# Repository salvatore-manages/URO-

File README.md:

# URO 🪐

A little AI companion for the real world.

«What if AI wasn't just inside our phones, but somthing we can actually carry with us?»

# 💡 About URO

URO is an AI wearable I'm trying to build. The idea is to make a small device that you can talk to, ask questions, take pictures with, and get AI-powered responces without having to do everything on your phone.

It's supposed to connect with an Android app, which handles the AI, internet and other processings, while the device itself handles voice input, audio output, camera and comunication.

I'm still figuring out alot of things, but that's what makes this project intresting to me.

# ✨ Features I'm Working On

- 🎙️ Voice interaction in English, Hindi and Hinglish.
- 🧠 AI-powered conversations and research using Gemini.
- 📸 Camera for taking pictures and asking questions about them.
- 🔊 Audio responces through a small speaker.
- 📱 Android application for connecting everything together.
- 🔵 Bluetooth comunication between the device and phone.
- 🎭 An animated AI character with its own personality.

# ⚙️ How It Works

Voice / Photo
      ↓
   URO Device
      ↓ Bluetooth
 Android App
      ↓
  Gemini AI
      ↓
Response → App → URO

# 🛠️ Tech & Hardware

Component| Technology
Microcontroller| ESP32-S3 (planned)
AI| Gemini
Connectivity| Bluetooth LE
Application| Android
Firmware| Embedded C/C++
PCB| Custom PCB design
Enclosure| 3D CAD design

# 🚧 Current Status

URO is currently in its design and developement phase. I'm working on the PCB, schematics, CAD, firmware and the software architechture.

The physical prototype isn't build yet. There is still alot to figure out, test and probably redesign.

🌱 Why I'm Building It

I'm a student trying to build something way beyond what I already know, and honestly, I'm learning as I go.

This project is my attempt to bring together AI, electronics, software and design into something real. I don't know exactly how difficult every part will be, but I want to try, make mistakes, fix them and see where this idea goes.

This is URO. Still building, still learning.

---

Built with curiosity, countless ideas and a lot of debugging.
(hehehe I'm kinda intelligent bruhh)
# Cooked by Raghav

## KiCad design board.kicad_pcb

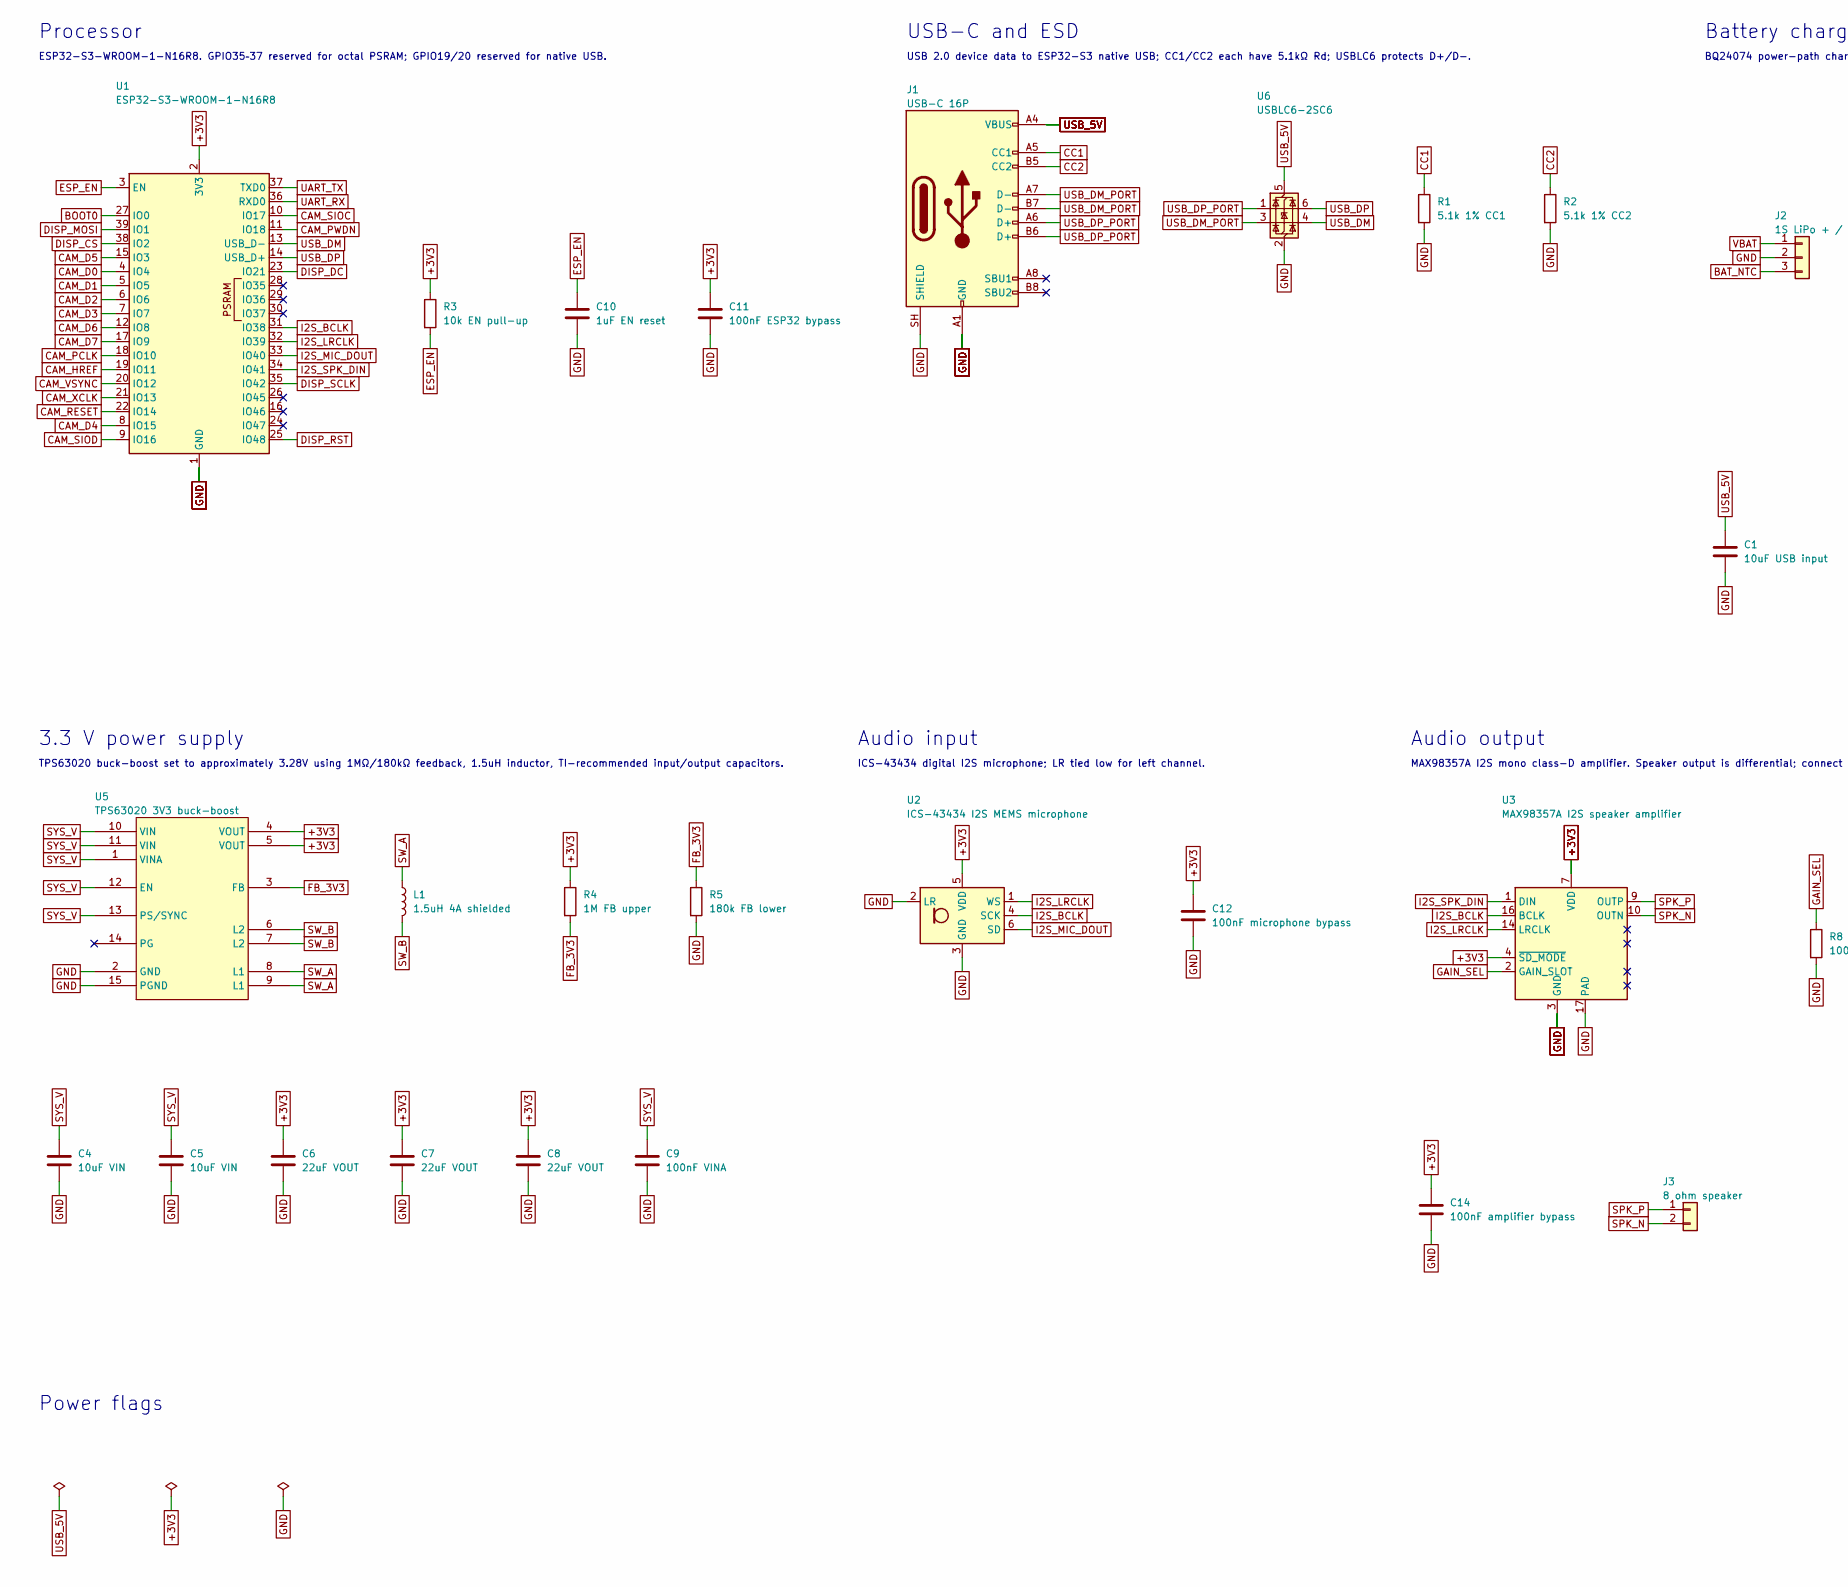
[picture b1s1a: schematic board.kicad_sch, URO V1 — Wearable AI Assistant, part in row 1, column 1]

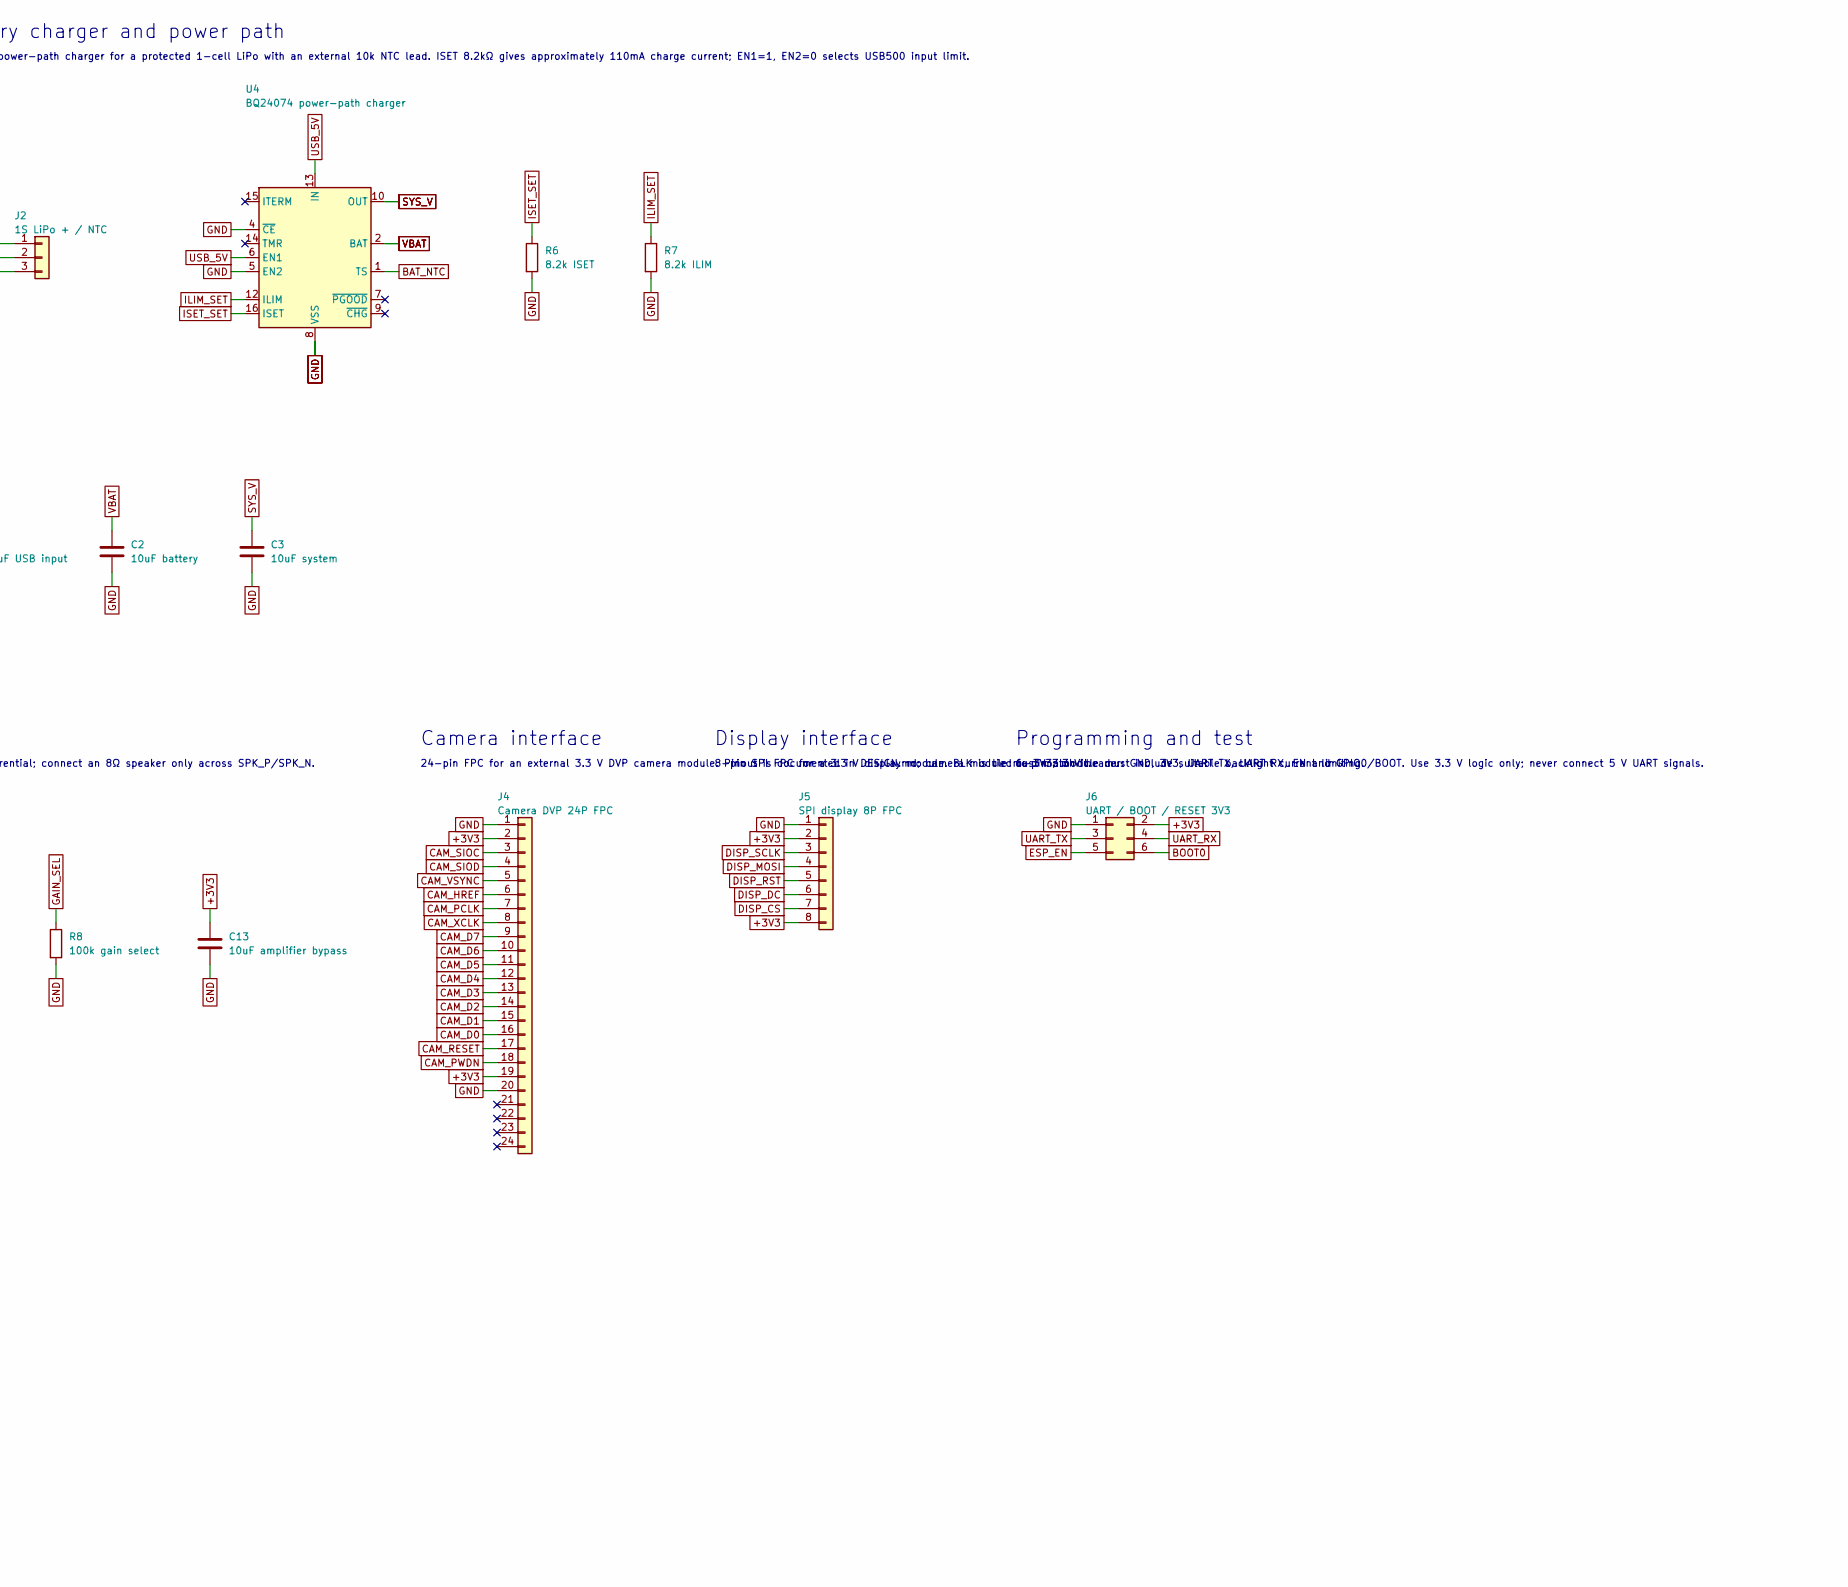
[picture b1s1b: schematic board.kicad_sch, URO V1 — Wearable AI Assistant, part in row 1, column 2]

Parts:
C1: 10uF USB input; C_0805_2012Metric
C2: 10uF battery; C_0805_2012Metric
C3: 10uF system; C_0805_2012Metric
C4, C5: 10uF VIN; C_0805_2012Metric
C6, C7, C8: 22uF VOUT; C_0805_2012Metric
C9: 100nF VINA; C_0603_1608Metric
C10: 1uF EN reset; C_0603_1608Metric
C11: 100nF ESP32 bypass; C_0603_1608Metric
C12: 100nF microphone bypass; C_0603_1608Metric
C13: 10uF amplifier bypass; C_0805_2012Metric
C14: 100nF amplifier bypass; C_0603_1608Metric
J1: USB-C 16P; USB_C_Receptacle_HRO_TYPE-C-31-M-12; MPN TYPE-C-31-M-12
J2: 1S LiPo + / NTC; JST_PH_B3B-PH-K_1x03_P2.00mm_Vertical; MPN JST PH 3-pin battery connector
J3: 8 ohm speaker; JST_PH_S2B-PH-K_1x02_P2.00mm_Horizontal
J4: Camera DVP 24P FPC; Hirose_FH12-24S-0.5SH_1x24-1MP_P0.50mm_Horizontal
J5: SPI display 8P FPC; Hirose_FH12-8S-0.5SH_1x08-1MP_P0.50mm_Horizontal
J6: UART / BOOT / RESET 3V3; PinHeader_2x03_P2.54mm_Vertical
L1: 1.5uH 4A shielded; L_1210_3225Metric; MPN FPB322520D-1R5MT0; LCSC C29780742
R1: 5.1k 1% CC1; R_0603_1608Metric; MPN 0603 5.1k 1%; LCSC C23186
R2: 5.1k 1% CC2; R_0603_1608Metric; MPN 0603 5.1k 1%; LCSC C23186
R3: 10k EN pull-up; R_0603_1608Metric
R4: 1M FB upper; R_0603_1608Metric
R5: 180k FB lower; R_0603_1608Metric
R6: 8.2k ISET; R_0603_1608Metric
R7: 8.2k ILIM; R_0603_1608Metric
R8: 100k gain select; R_0603_1608Metric
U1: ESP32-S3-WROOM-1-N16R8; ESP32-S3-WROOM-1; MPN ESP32-S3-WROOM-1-N16R8; LCSC C2913202
U2: ICS-43434 I2S MEMS microphone; MIC-SMD_6P-L3.5-W2.7-P0.90-BL; MPN ICS-43434; LCSC C5656610
U3: MAX98357A I2S speaker amplifier; TQFN-16-1EP_3x3mm_P0.5mm_EP1.23x1.23mm; MPN MAX98357AETE+T; LCSC C910544
U4: BQ24074 power-path charger; VQFN-16-1EP_3x3mm_P0.5mm_EP1.6x1.6mm; MPN BQ24074RGTT; LCSC C2861252
U5: TPS63020 3V3 buck-boost; VSON-14_L4.0-W3.0-P0.50-BL-EP_TI_DSJ; MPN TPS63020DSJR; LCSC C15483
U6: USBLC6-2SC6; SOT-23-6; MPN USBLC6-2SC6; LCSC C2687116

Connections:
+3V3: C6.1, C7.1, C8.1, C11.1, C12.1, C13.1, C14.1, J4.2, J4.19, J5.2, J5.8, J6.2, R3.1, R4.1, U1.2 (3V3), U2.5 (VDD), U3.4 (~SD_MODE), U3.7 (VDD), U3.8 (VDD), U5.4 (VOUT), U5.5 (VOUT)
BAT_NTC: J2.3, U4.1 (TS)
BOOT0: J6.6, U1.27 (IO0)
CAM_D0: J4.16, U1.4 (IO4)
CAM_D1: J4.15, U1.5 (IO5)
CAM_D2: J4.14, U1.6 (IO6)
CAM_D3: J4.13, U1.7 (IO7)
CAM_D4: J4.12, U1.8 (IO15)
CAM_D5: J4.11, U1.15 (IO3)
CAM_D6: J4.10, U1.12 (IO8)
CAM_D7: J4.9, U1.17 (IO9)
CAM_HREF: J4.6, U1.19 (IO11)
CAM_PCLK: J4.7, U1.18 (IO10)
CAM_PWDN: J4.18, U1.11 (IO18)
CAM_RESET: J4.17, U1.22 (IO14)
CAM_SIOC: J4.3, U1.10 (IO17)
CAM_SIOD: J4.4, U1.9 (IO16)
CAM_VSYNC: J4.5, U1.20 (IO12)
CAM_XCLK: J4.8, U1.21 (IO13)
CC1: J1.A5 (CC1), R1.1
CC2: J1.B5 (CC2), R2.1
DISP_CS: J5.7, U1.38 (IO2)
DISP_DC: J5.6, U1.23 (IO21)
DISP_MOSI: J5.4, U1.39 (IO1)
DISP_RST: J5.5, U1.25 (IO48)
DISP_SCLK: J5.3, U1.35 (IO42)
ESP_EN: C10.1, J6.5, R3.2, U1.3 (EN)
FB_3V3: R4.2, R5.1, U5.3 (FB)
GAIN_SEL: R8.1, U3.2 (GAIN_SLOT)
GND: C1.2, C2.2, C3.2, C4.2, C5.2, C6.2, C7.2, C8.2, C9.2, C10.2, C11.2, C12.2, C13.2, C14.2, J1.A1 (GND), J1.A12 (GND), J1.B1 (GND), J1.B12 (GND), J1.SH (SHIELD), J2.2, J4.1, J4.20, J5.1, J6.1, R1.2, R2.2, R5.2, R6.2, R7.2, R8.2, U1.1 (GND), U1.40 (GND), U1.41 (GND), U2.2 (LR), U2.3 (GND), U3.3 (GND), U3.11 (GND), U3.15 (GND), U3.17 (PAD), U4.4 (~CE), U4.5 (EN2), U4.8 (VSS), U4.17 (VSS), U5.2 (GND), U5.15 (PGND), U6.2 (GND)
I2S_BCLK: U1.31 (IO38), U2.4 (SCK), U3.16 (BCLK)
I2S_LRCLK: U1.32 (IO39), U2.1 (WS), U3.14 (LRCLK)
I2S_MIC_DOUT: U1.33 (IO40), U2.6 (SD)
I2S_SPK_DIN: U1.34 (IO41), U3.1 (DIN)
ILIM_SET: R7.1, U4.12 (ILIM)
ISET_SET: R6.1, U4.16 (ISET)
SPK_N: J3.2, U3.10 (OUTN)
SPK_P: J3.1, U3.9 (OUTP)
SW_A: L1.1, U5.8 (L1), U5.9 (L1)
SW_B: L1.2, U5.6 (L2), U5.7 (L2)
SYS_V: C3.1, C4.1, C5.1, C9.1, U4.10 (OUT), U4.11 (OUT), U5.1 (VINA), U5.10 (VIN), U5.11 (VIN), U5.12 (EN), U5.13 (PS/SYNC)
UART_RX: J6.4, U1.36 (RXD0)
UART_TX: J6.3, U1.37 (TXD0)
USB_5V: C1.1, J1.A4 (VBUS), J1.A9 (VBUS), J1.B4 (VBUS), J1.B9 (VBUS), U4.6 (EN1), U4.13 (IN), U6.5 (VBUS)
USB_DM: U1.13 (USB_D-), U6.4 (I/O2)
USB_DM_PORT: J1.A7 (D-), J1.B7 (D-), U6.3 (I/O2)
USB_DP: U1.14 (USB_D+), U6.6 (I/O1)
USB_DP_PORT: J1.A6 (D+), J1.B6 (D+), U6.1 (I/O1)
VBAT: C2.1, J2.1, U4.2 (BAT), U4.3 (BAT)

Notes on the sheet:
Processor
ESP32-S3-WROOM-1-N16R8. GPIO35–37 reserved for octal PSRAM; GPIO19/20 reserved for native USB.
USB-C and ESD
USB 2.0 device data to ESP32-S3 native USB; CC1/CC2 each have 5.1kΩ Rd; USBLC6 protects D+/D−.
Battery charger and power path
BQ24074 power-path charger for a protected 1-cell LiPo with an external 10k NTC lead. ISET 8.2kΩ gives approximately 110mA charge current; EN1=1, EN2=0 selects USB500 input limit.
3.3 V power supply
TPS63020 buck-boost set to approximately 3.28V using 1MΩ/180kΩ feedback, 1.5uH inductor, TI-recommended input/output capacitors.
Audio input
ICS-43434 digital I2S microphone; LR tied low for left channel.
Audio output
MAX98357A I2S mono class-D amplifier. Speaker output is differential; connect an 8Ω speaker only across SPK_P/SPK_N.
Camera interface
24-pin FPC for an external 3.3 V DVP camera module. Pinout is documented in DESIGN.md; camera module must match it.
Display interface
8-pin SPI FPC for a 3.3 V display module. BLK is tied to 3V3; module must include suitable backlight current limiting.
Programming and test
6-pin 3.3 V header: GND, 3V3, UART TX, UART RX, EN and GPIO0/BOOT. Use 3.3 V logic only; never connect 5 V UART signals.
Power flags

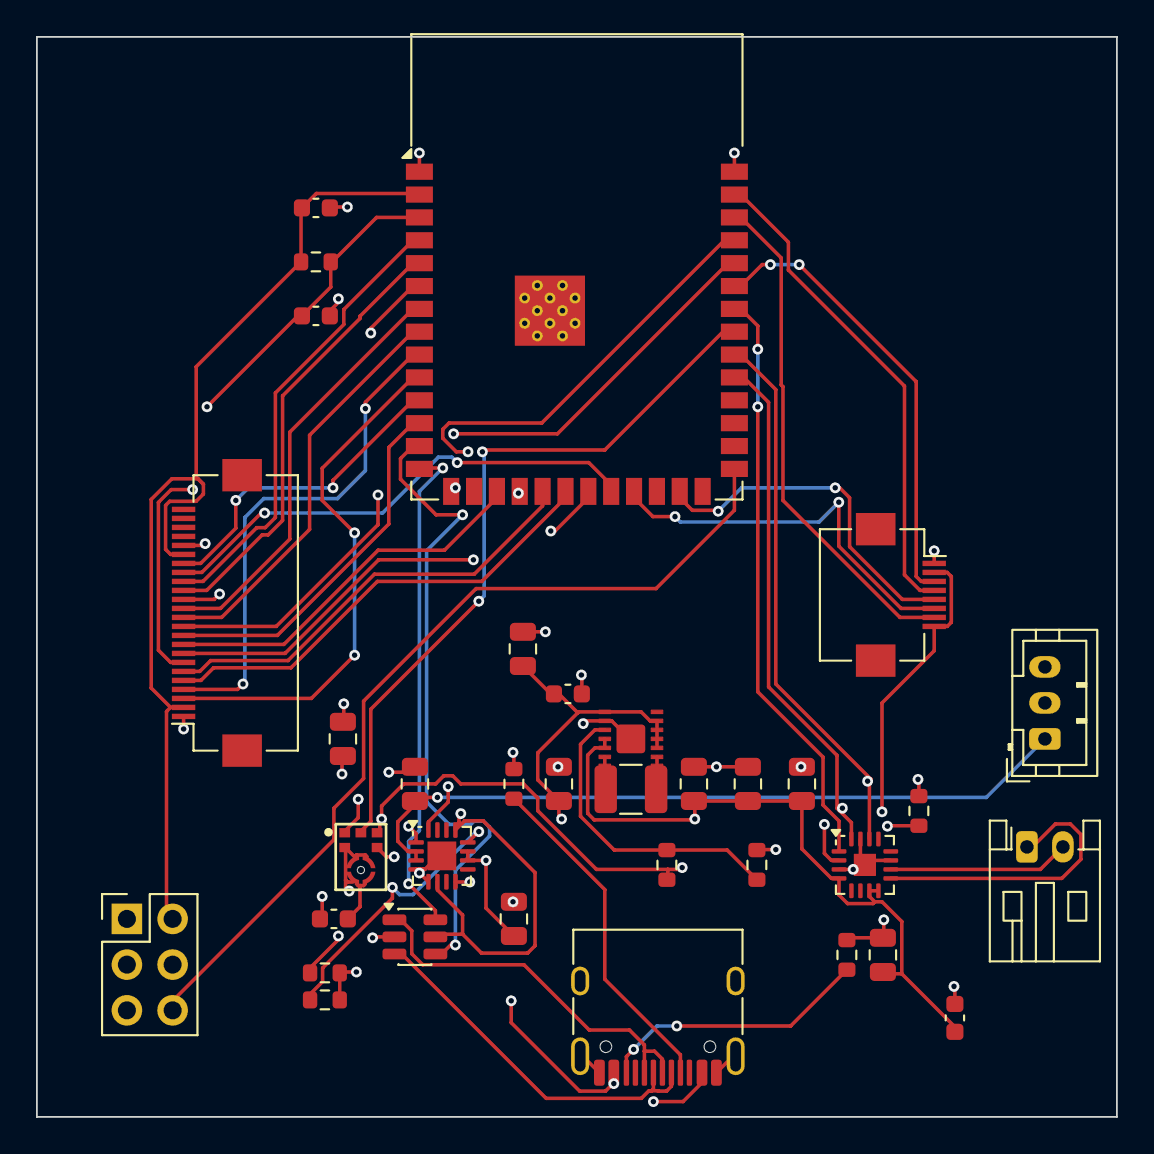
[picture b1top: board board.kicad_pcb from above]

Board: 4 copper layers, 60.0 x 60.0 mm, 35 parts (0 on the bottom side), 49 nets.

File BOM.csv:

Designators,Value,Manufacturer Part Number,Footprint,Qty,LCSC Part Number,Notes
C1,10uF USB input,,Capacitor_SMD:C_0805_2012Metric,1,,Manufacturer part number and electrical rating are not specified; select and verify before ordering.
C10,1uF EN reset,,Capacitor_SMD:C_0603_1608Metric,1,,Manufacturer part number and electrical rating are not specified; select and verify before ordering.
C11,100nF ESP32 bypass,,Capacitor_SMD:C_0603_1608Metric,1,,Manufacturer part number and electrical rating are not specified; select and verify before ordering.
C12,100nF microphone bypass,,Capacitor_SMD:C_0603_1608Metric,1,,Manufacturer part number and electrical rating are not specified; select and verify before ordering.
C13,10uF amplifier bypass,,Capacitor_SMD:C_0805_2012Metric,1,,Manufacturer part number and electrical rating are not specified; select and verify before ordering.
C14,100nF amplifier bypass,,Capacitor_SMD:C_0603_1608Metric,1,,Manufacturer part number and electrical rating are not specified; select and verify before ordering.
C2,10uF battery,,Capacitor_SMD:C_0805_2012Metric,1,,Manufacturer part number and electrical rating are not specified; select and verify before ordering.
C3,10uF system,,Capacitor_SMD:C_0805_2012Metric,1,,Manufacturer part number and electrical rating are not specified; select and verify before ordering.
"C4, C5",10uF VIN,,Capacitor_SMD:C_0805_2012Metric,2,,Manufacturer part number and electrical rating are not specified; select and verify before ordering.
"C6, C7, C8",22uF VOUT,,Capacitor_SMD:C_0805_2012Metric,3,,Manufacturer part number and electrical rating are not specified; select and verify before ordering.
C9,100nF VINA,,Capacitor_SMD:C_0603_1608Metric,1,,Manufacturer part number and electrical rating are not specified; select and verify before ordering.
J1,USB-C 16P,TYPE-C-31-M-12,Connector_USB:USB_C_Receptacle_HRO_TYPE-C-31-M-12,1,,
J2,1S LiPo + / NTC,JST PH 3-pin battery connector,parts:JST_PH_B3B-PH-K_1x03_P2.00mm_Vertical,1,,Requires a protected 1-cell LiPo pack with compatible 10k NTC lead; verify connector polarity and pack dimensions.
J3,8 ohm speaker,,parts:JST_PH_S2B-PH-K_1x02_P2.00mm_Horizontal,1,,Speaker connector only; verify speaker impedance and rated power before fitting.
J4,Camera DVP 24P FPC,,Connector_FFC-FPC:Hirose_FH12-24S-0.5SH_1x24-1MP_P0.50mm_Horizontal,1,,Connector only. Camera sensor/module and flex contact orientation are not yet selected.
J5,SPI display 8P FPC,,Connector_FFC-FPC:Hirose_FH12-8S-0.5SH_1x08-1MP_P0.50mm_Horizontal,1,,"Connector only. Display controller, resolution, flex orientation and backlight current must be confirmed."
J6,UART / BOOT / RESET 3V3,,Connector_PinHeader_2.54mm:PinHeader_2x03_P2.54mm_Vertical,1,,"2x3 programming header: GND, 3V3, UART_TX, UART_RX, ESP_EN, BOOT0. 3.3V logic only."
L1,1.5uH 4A shielded,FPB322520D-1R5MT0,Inductor_SMD:L_1210_3225Metric,1,C29780742,
R1,5.1k 1% CC1,0603 5.1k 1%,Resistor_SMD:R_0603_1608Metric,1,C23186,
R2,5.1k 1% CC2,0603 5.1k 1%,Resistor_SMD:R_0603_1608Metric,1,C23186,
R3,10k EN pull-up,,Resistor_SMD:R_0603_1608Metric,1,,Manufacturer part number and electrical rating are not specified; select and verify before ordering.
R4,1M FB upper,,Resistor_SMD:R_0603_1608Metric,1,,Manufacturer part number and electrical rating are not specified; select and verify before ordering.
R5,180k FB lower,,Resistor_SMD:R_0603_1608Metric,1,,Manufacturer part number and electrical rating are not specified; select and verify before ordering.
R6,8.2k ISET,,Resistor_SMD:R_0603_1608Metric,1,,Manufacturer part number and electrical rating are not specified; select and verify before ordering.
R7,8.2k ILIM,,Resistor_SMD:R_0603_1608Metric,1,,Manufacturer part number and electrical rating are not specified; select and verify before ordering.
R8,100k gain select,,Resistor_SMD:R_0603_1608Metric,1,,Manufacturer part number and electrical rating are not specified; select and verify before ordering.
U1,ESP32-S3-WROOM-1-N16R8,ESP32-S3-WROOM-1-N16R8,RF_Module:ESP32-S3-WROOM-1,1,C2913202,ESP32-S3-WROOM-1-N16R8 module; verify exact module marking and antenna keep-out.
U2,ICS-43434 I2S MEMS microphone,ICS-43434,parts:MIC-SMD_6P-L3.5-W2.7-P0.90-BL,1,C5656610,
U3,MAX98357A I2S speaker amplifier,MAX98357AETE+T,parts:TQFN-16-1EP_3x3mm_P0.5mm_EP1.23x1.23mm,1,C910544,
U4,BQ24074 power-path charger,BQ24074RGTT,parts:VQFN-16-1EP_3x3mm_P0.5mm_EP1.6x1.6mm,1,C2861252,BQ24074 charger/power-path IC; use only with the specified protected 1-cell battery arrangement.
U5,TPS63020 3V3 buck-boost,TPS63020DSJR,parts:VSON-14_L4.0-W3.0-P0.50-BL-EP_TI_DSJ,1,C15483,TPS63020 buck-boost regulator; verify inductor and capacitor effective values under DC bias.
U6,USBLC6-2SC6,USBLC6-2SC6,parts:SOT-23-6,1,C2687116,

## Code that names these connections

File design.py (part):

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    s.part("J1", "Connector:USB_C_Receptacle_USB2.0_16P", "USB-C 16P",
           block="USB-C and ESD", footprint="Connector_USB:USB_C_Receptacle_HRO_TYPE-C-31-M-12",
           fields={"MPN":"TYPE-C-31-M-12","Datasheet":"https://www.usb.org/sites/default/files/documents/usb_type-c.zip"},
           pins={"A1":"GND","A4":"USB_5V","A5":"CC1","A6":"USB_DP_PORT","A7":"USB_DM_PORT",
                 "A8":None,"A9":"USB_5V","A12":"GND","B1":"GND","B4":"USB_5V","B5":"CC2",
                 "B6":"USB_DP_PORT","B7":"USB_DM_PORT","B8":None,"B9":"USB_5V","B12":"GND","SH":"GND"})
    s.part("U6", "parts:USBLC6-2SC6", "USBLC6-2SC6",
           block="USB-C and ESD", footprint="parts:SOT-23-6",
           fields={"MPN":"USBLC6-2SC6","LCSC":"C2687116","Datasheet":"https://www.st.com/resource/en/datasheet/usblc6-2.pdf"},
           pins={"1":"USB_DP_PORT","2":"GND","3":"USB_DM_PORT","4":"USB_DM","5":"USB_5V","6":"USB_DP"})
    s.part("R1","Device:R","5.1k 1% CC1",block="USB-C and ESD",
           footprint="Resistor_SMD:R_0603_1608Metric",fields={"MPN":"0603 5.1k 1%","LCSC":"C23186"},
           pins={"1":"CC1","2":"GND"})
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           block="Battery charger and power path",
           footprint="parts:JST_PH_B3B-PH-K_1x03_P2.00mm_Vertical",
           fields={"MPN":"JST PH 3-pin battery connector"},
           pins={"1":"VBAT","2":"GND","3":"BAT_NTC"})
    s.part("U4","parts:BQ24074RGT","BQ24074 power-path charger",
           block="Battery charger and power path",
           footprint="parts:VQFN-16-1EP_3x3mm_P0.5mm_EP1.6x1.6mm",
           fields={"MPN":"BQ24074RGTT","LCSC":"C2861252","Datasheet":"https://www.ti.com/lit/ds/symlink/bq24074.pdf"},
           pins={"1":"BAT_NTC","2":"VBAT","3":"VBAT","4":"GND","5":"GND","6":"USB_5V",
                 "7":None,"8":"GND","9":None,"10":"SYS_V","11":"SYS_V","12":"ILIM_SET",
                 "13":"USB_5V","14":None,"15":None,"16":"ISET_SET","17":"GND"})
    s.part("R6","Device:R","8.2k ISET",block="Battery charger and power path",
           footprint="Resistor_SMD:R_0603_1608Metric",pins={"1":"ISET_SET","2":"GND"})
    s.part("R7","Device:R","8.2k ILIM",block="Battery charger and power path",
           footprint="Resistor_SMD:R_0603_1608Metric",pins={"1":"ILIM_SET","2":"GND"})
    s.part("C1","Device:C","10uF USB input",block="Battery charger and power path",
           footprint="Capacitor_SMD:C_0805_2012Metric",pins={"1":"USB_5V","2":"GND"})
    s.part("C2","Device:C","10uF battery",block="Battery charger and power path",
           footprint="Capacitor_SMD:C_0805_2012Metric",pins={"1":"VBAT","2":"GND"})
    s.part("C3","Device:C","10uF system",block="Battery charger and power path",
           footprint="Capacitor_SMD:C_0805_2012Metric",pins={"1":"SYS_V","2":"GND"})

    # 3.3 V buck-boost. Values follow TI TPS63020 datasheet SLVS916I, pp. 3–4, 14–16.
    s.part("U5","parts:TI TPS63020","TPS63020 3V3 buck-boost",
           block="3.3 V power supply",
           footprint="parts:VSON-14_L4.0-W3.0-P0.50-BL-EP_TI_DSJ",
           fields={"MPN":"TPS63020DSJR","LCSC":"C15483","Datasheet":"https://www.ti.com/lit/ds/symlink/tps63020.pdf"},
           pins={"1":"SYS_V","2":"GND","3":"FB_3V3","4":"+3V3","5":"+3V3",
                 "6":"SW_B","7":"SW_B","8":"SW_A","9":"SW_A","10":"SYS_V","11":"SYS_V",
                 "12":"SYS_V","13":"SYS_V","14":None,"15":"GND"})
    s.part("L1","Device:L","1.5uH 4A shielded",block="3.3 V power supply",
           footprint="Inductor_SMD:L_1210_3225Metric",
           fields={"MPN":"FPB322520D-1R5MT0","LCSC":"C29780742"},
           pins={"1":"SW_A","2":"SW_B"})
    s.part("R4","Device:R","1M FB upper",block="3.3 V power supply",
           footprint="Resistor_SMD:R_0603_1608Metric",pins={"1":"+3V3","2":"FB_3V3"})
    s.part("R5","Device:R","180k FB lower",block="3.3 V power supply",
           footprint="Resistor_SMD:R_0603_1608Metric",pins={"1":"FB_3V3","2":"GND"})
    s.part("C4","Device:C","10uF VIN",block="3.3 V power supply",
           footprint="Capacitor_SMD:C_0805_2012Metric",pins={"1":"SYS_V","2":"GND"})
    s.part("C5","Device:C","10uF VIN",block="3.3 V power supply",
           footprint="Capacitor_SMD:C_0805_2012Metric",pins={"1":"SYS_V","2":"GND"})
    s.part("C6","Device:C","22uF VOUT",block="3.3 V power supply",
           footprint="Capacitor_SMD:C_0805_2012Metric",pins={"1":"+3V3","2":"GND"})
    s.part("C7","Device:C","22uF VOUT",block="3.3 V power supply",
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    s.part("C8","Device:C","22uF VOUT",block="3.3 V power supply",
           footprint="Capacitor_SMD:C_0805_2012Metric",pins={"1":"+3V3","2":"GND"})
    s.part("C9","Device:C","100nF VINA",block="3.3 V power supply",
           footprint="Capacitor_SMD:C_0603_1608Metric",pins={"1":"SYS_V","2":"GND"})

    # ESP32 enable/reset bias and local bypass.
    s.part("R3","Device:R","10k EN pull-up",block="Processor",
           footprint="Resistor_SMD:R_0603_1608Metric",pins={"1":"+3V3","2":"ESP_EN"})
    s.part("C10","Device:C","1uF EN reset",block="Processor",
           footprint="Capacitor_SMD:C_0603_1608Metric",pins={"1":"ESP_EN","2":"GND"})
    s.part("C11","Device:C","100nF ESP32 bypass",block="Processor",
           footprint="Capacitor_SMD:C_0603_1608Metric",pins={"1":"+3V3","2":"GND"})

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           block="Audio input",
           footprint="parts:MIC-SMD_6P-L3.5-W2.7-P0.90-BL",
           fields={"MPN":"ICS-43434","LCSC":"C5656610","Datasheet":"https://invensense.tdk.com/"},
           pins={"1":"I2S_LRCLK","2":"GND","3":"GND","4":"I2S_BCLK","5":"+3V3","6":"I2S_MIC_DOUT"})
    s.part("C12","Device:C","100nF microphone bypass",block="Audio input",
           footprint="Capacitor_SMD:C_0603_1608Metric",pins={"1":"+3V3","2":"GND"})

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           block="Audio output",
           footprint="parts:TQFN-16-1EP_3x3mm_P0.5mm_EP1.23x1.23mm",
           fields={"MPN":"MAX98357AETE+T","LCSC":"C910544","Datasheet":"https://www.analog.com/media/en/technical-documentation/data-sheets/MAX98357A.pdf"},
           pins={"1":"I2S_SPK_DIN","2":"GAIN_SEL","3":"GND","4":"+3V3",
                 "7":"+3V3","8":"+3V3","9":"SPK_P","10":"SPK_N",
                 "11":"GND","14":"I2S_LRCLK","15":"GND","16":"I2S_BCLK","17":"GND"})
    s.part("R8","Device:R","100k gain select",block="Audio output",
           footprint="Resistor_SMD:R_0603_1608Metric",pins={"1":"GAIN_SEL","2":"GND"})
    s.part("C13","Device:C","10uF amplifier bypass",block="Audio output",
           footprint="Capacitor_SMD:C_0805_2012Metric",pins={"1":"+3V3","2":"GND"})
    s.part("C14","Device:C","100nF amplifier bypass",block="Audio output",
           footprint="Capacitor_SMD:C_0603_1608Metric",pins={"1":"+3V3","2":"GND"})
    s.part("J3","Connector_Generic:Conn_01x02","8 ohm speaker",
           block="Audio output",footprint="parts:JST_PH_S2B-PH-K_1x02_P2.00mm_Horizontal",
           pins={"1":"SPK_P","2":"SPK_N"})

    # External camera daughterboard connector. Pinout is URO's defined DVP cable contract,
    # not a claim that every OV2640 breakout uses this pin order.
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    s.part("J5","Connector_Generic:Conn_01x08","SPI display 8P FPC",
           block="Display interface",footprint="Connector_FFC-FPC:Hirose_FH12-8S-0.5SH_1x08-1MP_P0.50mm_Horizontal",
           fields={"Description":"URO SPI display cable pinout"},
           pins={"1":"GND","2":"+3V3","3":"DISP_SCLK","4":"DISP_MOSI",
                 "5":"DISP_RST","6":"DISP_DC","7":"DISP_CS","8":"+3V3"})
    s.note("Display interface","8-pin SPI FPC for a 3.3 V display module. BLK is tied to 3V3; module must include suitable backlight current limiting.")

    # UART programming/debug header (3.3 V USB-UART adapter only).
    s.part("J6","Connector_Generic:Conn_02x03_Odd_Even","UART / BOOT / RESET 3V3",
           block="Programming and test",footprint="Connector_PinHeader_2.54mm:PinHeader_2x03_P2.54mm_Vertical",
           pins={"1":"GND","2":"+3V3","3":"UART_TX","4":"UART_RX","5":"ESP_EN","6":"BOOT0"})
    s.note("Programming and test","6-pin 3.3 V header: GND, 3V3, UART TX, UART RX, EN and GPIO0/BOOT. Use 3.3 V logic only; never connect 5 V UART signals.")

    s.note("USB-C and ESD","USB 2.0 device data to ESP32-S3 native USB; CC1/CC2 each have 5.1kΩ Rd; USBLC6 protects D+/D−.")
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
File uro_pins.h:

#pragma once

// URO V1 Rev 3 pin contract from DESIGN.md. Verify against the assembled PCB.
namespace uro {
// Programming strap; exposed as J6 pad 6, not driven by application firmware.
constexpr int BOOT0 = 0;
// I2S microphone + speaker share clocks.
constexpr int I2S_BCLK = 38;
constexpr int I2S_WS = 39;
constexpr int I2S_MIC_DATA = 40;
constexpr int I2S_SPK_DIN = 41;

// SPI display connector J5.
constexpr int DISP_SCLK = 42;
constexpr int DISP_MOSI = 1;
constexpr int DISP_CS = 2;
constexpr int DISP_DC = 21;
constexpr int DISP_RESET = 48;

// DVP camera connector J4.
constexpr int CAM_D0 = 4;
constexpr int CAM_D1 = 5;
constexpr int CAM_D2 = 6;
constexpr int CAM_D3 = 7;
constexpr int CAM_D4 = 15;
constexpr int CAM_D5 = 3;
constexpr int CAM_D6 = 8;
constexpr int CAM_D7 = 9;
constexpr int CAM_PCLK = 10;
constexpr int CAM_HREF = 11;
constexpr int CAM_VSYNC = 12;
constexpr int CAM_XCLK = 13;
constexpr int CAM_RESET = 14;
constexpr int CAM_PWDN = 18;
constexpr int CAM_SCCB_SCL = 17;
constexpr int CAM_SCCB_SDA = 16;
}
